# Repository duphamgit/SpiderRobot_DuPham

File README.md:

# SpiderRobot_DuPham
This is Spider Robot made by Du Pham

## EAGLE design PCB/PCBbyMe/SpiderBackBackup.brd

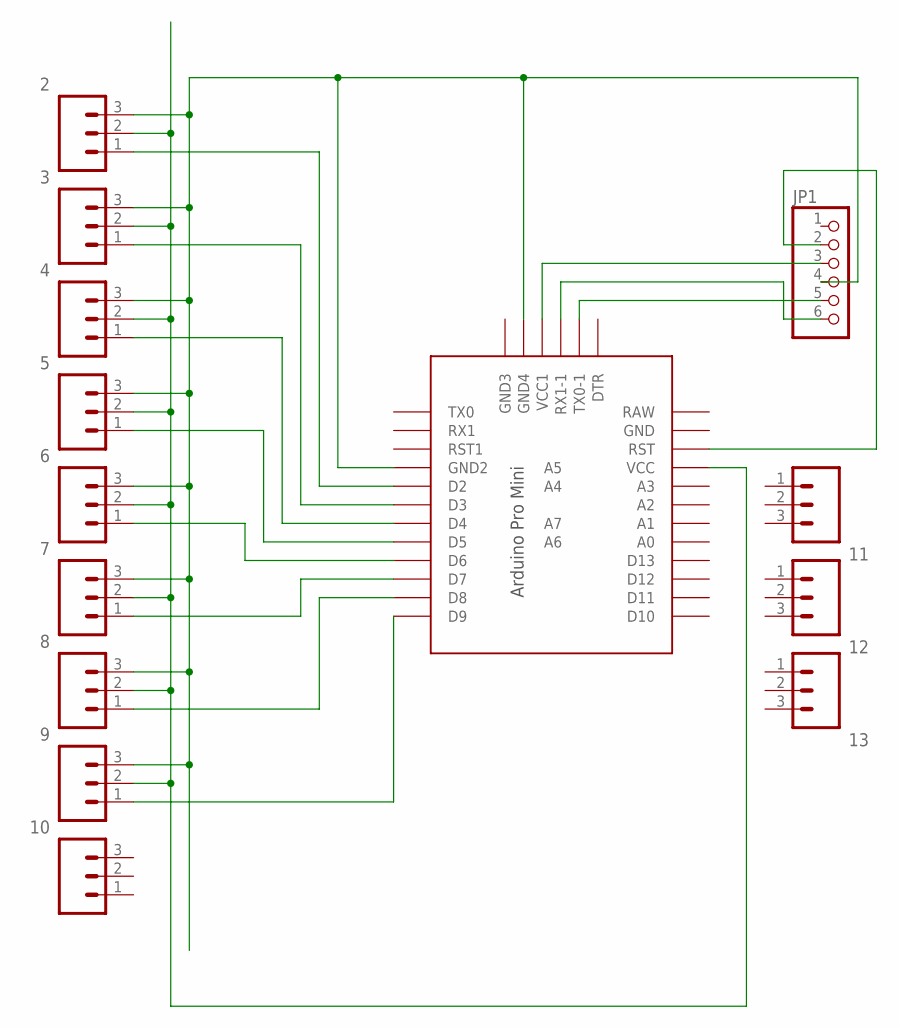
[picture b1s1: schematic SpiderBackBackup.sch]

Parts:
2, 3, 4, 5, 6, 7, 8, 9, 10, 11, 12, 13: M03PTH; 1X03
JP1: PINHD-1X6CB; 1X06-CLEANBIG
U$1: PRO-MINI-2

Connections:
unnamed: 3.1, U$1.D3
unnamed: 2.1, U$1.D2
unnamed: 7.1, U$1.D7
unnamed: 4.1, U$1.D4
unnamed: 5.1, U$1.D5
unnamed: 6.1, U$1.D6
unnamed: 8.1, U$1.D8
unnamed: 9.1, U$1.D9
unnamed: JP1.6, U$1.RX1-1
unnamed: JP1.5, U$1.TX0-1
unnamed: 2.3, 3.3, 4.3, 5.3, 6.3, 7.3, 8.3, 9.3, JP1.4, U$1.GND1 (GND2), U$1.GND3 (GND4)
unnamed: JP1.3, U$1.VCC1
unnamed: JP1.2, U$1.RST
unnamed: 2.2, 3.2, 4.2, 5.2, 6.2, 7.2, 8.2, 9.2, U$1.VCC

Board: 2 copper layers, 14 parts (0 on the bottom side), 14 nets, no tracks yet.

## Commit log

2017-09-28 Create Project Structure
    Create Project Structure
2017-09-28 Done Project Structure
    Done Project Structure
2017-10-11 Update Led and Ultrasonic SRF05 Module
    Now Spider have 1 led and it can avoid barrier
